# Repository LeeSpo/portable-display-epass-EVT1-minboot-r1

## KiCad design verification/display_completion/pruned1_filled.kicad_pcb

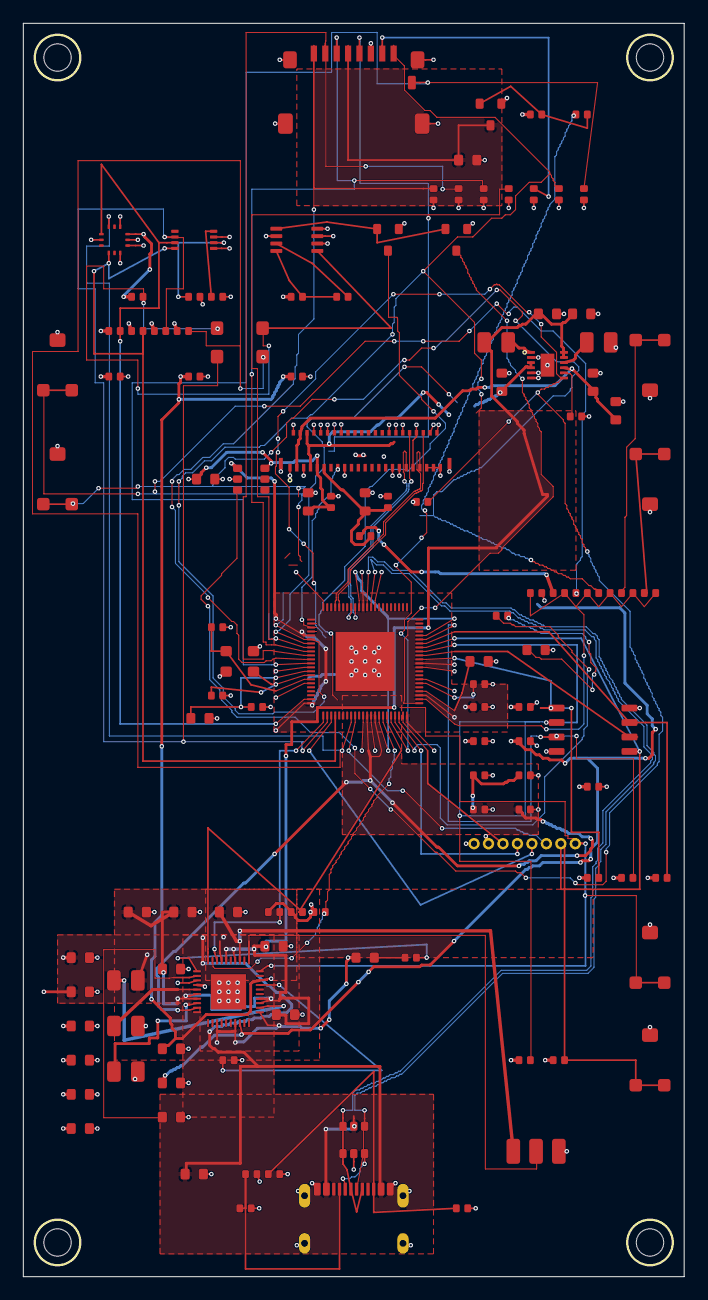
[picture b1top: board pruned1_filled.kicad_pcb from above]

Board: 4 copper layers, 58.0 x 110.0 mm, 124 parts (0 on the bottom side), 83 nets.

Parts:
C1, C2, C4, C5, C6, C7, C8, C9: 22u; 0603
C3, C11, C33, C40, C41, C42, C44: 1u; 0603
C10, C34, C35, C38: 2.2u; 0603
C12, C13: 18p; 0402
C14, C15, C16, C17, C18, C19, C20, C21, C22, C23, C24, C25, C26, C37, C39, C43, C45, C51: 100n; 0402
C29: 4.7u; 0603
C30, C32, C46, C47, C48, C49, C50: 10u; 0603
C31: 10n; 0402
C36: 470n; 0402
D1: CHARGE; LED0603
D2, D3: BAT54; D_SOD123
D5: STATUS; LED0603
D6, D7, D8, D9, D10, D11, D12, D13, D14: PESD4V0; 0402
H1: M2; MountingHole_1
H2: M2; MountingHole_2
H3: M2; MountingHole_3
H4: M2; MountingHole_4
J1: USB4105-GF-A-060; USB4105
J2: 1S LiPo + NTC; BAT3
J3: DEBUG POGO; HDR8
J4: KD024EGOIN152-01; FPC45
J5: MicroSD; MICROSD
L1, L2, L3: 1uH/2A; IND_2x2
L5, L6: 4.7uH; IND_2x2
Q1, Q2: 2N7002; SOT23-3
Q3: AO3401A; SOT23-3
R1, R2: 5.1k; 0402
R3, R15, R16: 4.7k; 0402
R4, R5, R6, R27: 2.2k; 0402
R7, R8, R9, R10, R11, R13, R14, R17, R18, R21, R28: 10k; 0402
R12: 820k; 0402
R20, R22, R26: 100k; 0402
R23, R29, R31: 0R; 0402
R24: 22k; 0402
R25: 47k; 0402
SW1: UP; SW_SIDE
SW2: DOWN; SW_SIDE
SW3: OK; SW_SIDE
SW4: BACK; SW_SIDE
SW5: POWER; SW_SIDE
SW6: FEL; SW_SIDE
U1: AXP2101; QFN40
U2: V851s; QFN88
U3: W25N01GVZEIG; WSON-8
U4: LIS2DW12TR; LGA-12
U5: RV-3028-C7; RTC-8
U6: SN74LVC1G123DCTR; SSOP-8
U8: TPS22918DBVR; SOT23-6
U9: USBLC6-2SC6; SOT23-6
U10: TPS65631DPDR; WSON-12
Y1: 24MHz 10ppm; XTAL4

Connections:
1V8: C10.1, C16.1, C17.1, R22.1, R29.1, U1.18 (ALDO1)
3V3: C4.1, C5.1, C14.1, C15.1, C22.1, D1.1, J3.2 (3V3), L1.2, Q3.2 (S), R3.1, R4.1, R5.1, R7.1, R8.1, R9.1, R10.1, R15.1, R16.1, R17.1, R18.1, R20.1, R28.1, U1.13 (BLDOIN), U1.17 (ALDOIN), U1.21 (FB1), U2.5 (VCC33_PF_PD), U2.22 (VCC_PE), U2.44 (VCC_IO), U2.47 (VDD33), U2.55 (VCC_PC), U2.78 (VCC33_USB), U3.8 (VCC), U8.1 (VIN)
ACCEL_INT_N: D3.1, R18.2, U2.30 (PE6), U4.12 (INT1)
ADC_KEYS: C31.1, R22.2, R23.2, R24.2, R25.2, R26.2, U2.46 (GPADC0)
BAT_NTC: J2.2 (NTC), U1.31 (TS)
CHGLED_A: D1.2, R6.1
CHGLED_N: R6.2, U1.1 (CHGLED)
CORE_0V93: C6.1, C7.1, C18.1, C19.1, C20.1, L2.2, U1.4 (FB3), U2.13 (VDD_SYS0), U2.17 (VDD_SYS1), U2.33 (VDD_SYS2), U2.35 (VDD_SYS3), U2.54 (VDD_SYS4), U2.75 (VDD_SYS5), U2.88 (VDD_SYS6)
DRAM_1V5: C8.1, C9.1, C21.1, L3.2, U1.9 (FB4), U2.34 (VCC_DRAM0), U2.36 (VCC_DRAM1)
DSI_CKN: J4.40 (CLKN), U2.84 (PD5_DSI_CKN)
DSI_CKP: J4.39 (CLKP), U2.85 (PD6_DSI_CKP)
DSI_D0N: J4.36 (D0N), U2.80 (PD1_DSI_D0N)
DSI_D0P: J4.35 (D0P), U2.81 (PD2_DSI_D0P)
E907_RX: J3.6 (E907_RX), U2.31 (PE1)
E907_TX: J3.5 (E907_TX), U2.25 (PE0)
ELVDD: C48.1, J4.6 (ELVDD), J4.7 (ELVDD), U10.3 (OUTP), U10.4 (FBS)
ELVSS: C49.1, C50.1, J4.3 (ELVSS), J4.4 (ELVSS), U10.9 (OUTN)
EL_CT: C51.1, U10.8 (CT)
EL_SWN: L6.1, U10.10 (SWN)
EL_SWP: L5.2, U10.1 (SWP)
GND: C1.2, C2.2, C3.2, C4.2, C5.2, C6.2, C7.2, C8.2, C9.2, C10.2, C11.2, C12.2, C13.2, C14.2, C15.2, C16.2, C17.2, C18.2, C19.2, C20.2, C21.2, C22.2, C24.2, C25.2, C26.2, C29.2, C30.2, C31.2, C32.2, C33.2, C34.2, C35.2, C36.2, C37.2, C38.2, C39.2, C40.2, C41.2, C42.2, C43.2, C44.2, C45.2, C46.2, C47.2, C48.2, C49.2, C50.2, C51.2, D5.2, D6.2, D7.2, D8.2, D9.2, D10.2, D11.2, D12.2, D13.2, D14.2, J1.A1 (GND), J1.A12 (GND), J1.B1 (GND), J1.B12 (GND), J1.SH1 (SHIELD), J1.SH2 (SHIELD), J1.SH3 (SHIELD), J1.SH4 (SHIELD), J2.3 (GND), J3.1 (GND), J4.1 (GND), J4.2 (GND), J4.5 (GND), J4.8 (GND), J4.10 (GND), J4.12 (GND), J4.17 (GND), J4.30 (GND), J4.31 (IM1), J4.32 (IM0), J4.33 (GND), J4.34 (GND), J4.37 (GND), J4.38 (GND), J4.41 (GND), J4.42 (GND), J4.43 (MTP), J4.44 (GND), J4.45 (GND), J4.MP1 (MOUNT), J4.MP2 (MOUNT), J5.6 (VSS), J5.10 (SH), J5.11 (SH), J5.12 (SH), J5.13 (SH), L6.2, Q1.2 (S), Q2.2 (S), R1.2, R2.2, R13.2, R14.2, SW1.3 (GND), SW2.3 (GND), SW3.3 (GND), SW4.3 (GND), SW5.3 (GND), SW6.3 (GND), U1.3 (GND), U1.41 (EPAD), U2.51 (AGND), U2.89 (EPAD), U3.4 (GND), U4.6 (GND), U4.7 (RES), U4.8 (GND), U5.5 (VSS), U6.2 (GND), U8.2 (GND), U9.2 (GND), U10.2 (PGND), U10.5 (AGND), U10.6 (GND), U10.13 (EPAD), Y1.2 (GND), Y1.4 (GND)
I2C0_SCL: R15.2, U2.21 (PE4), U4.1 (SCL), U5.3 (SCL)
I2C0_SDA: R16.2, U2.26 (PE5), U4.4 (SDA), U5.4 (SDA)
KEY_BACK: R26.1, SW4.1 (KEY), SW4.2 (KEY)
KEY_DOWN: R24.1, SW2.1 (KEY), SW2.2 (KEY)
KEY_OK: R25.1, SW3.1 (KEY), SW3.2 (KEY)
KEY_UP: R23.1, SW1.1 (KEY), SW1.2 (KEY)
LCD_1V8: C44.1, C45.1, J4.11 (VDDIO), R29.2
LCD_3V3: C29.1, C42.1, C43.1, J4.9 (VCI), U8.6 (VOUT)
LCD_EN: R31.2, U2.4 (PD21), U8.3 (ON), U10.7 (CTRL)
LCD_RST: J4.16 (RESX), U2.2 (PD19)
LCD_SWIRE: J4.14 (SWIRE), R31.1
LCD_TE: J4.15 (TE), U2.3 (PD20)
LX_3V3: L1.1, U1.22 (LX1)
LX_CORE: L2.1, U1.5 (LX3)
LX_DRAM: L3.1, U1.8 (LX4)
NAND_CLK: U2.57 (PC0_SPI0_CLK), U3.6 (CLK)
NAND_CS: R7.2, U2.56 (PC1_SPI0_CS), U3.1 (CS)
NAND_HOLD: R9.2, U2.60 (PC5_SPI0_HOLD), U3.7 (HOLD)
NAND_MISO: R28.2, U2.58 (PC3_SPI0_MISO_BOOT1), U3.2 (MISO)
NAND_MOSI: J3.7 (FEL_PC2), R10.2, SW6.1 (FEL_PC2), SW6.2 (FEL_PC2), U2.59 (PC2_SPI0_MOSI_BOOT0), U3.5 (MOSI)
NAND_WP: R8.2, U2.61 (PC4_SPI0_WP), U3.3 (WP)
PMIC_BACKUP: C39.1, U1.27 (VBACKUP)
PMIC_IRQ_N: R3.2, U1.38 (IRQ), U2.23 (PE2)
PMIC_SCL: R4.2, U1.40 (SCK), U2.39 (PH13)
PMIC_SDA: R5.2, U1.39 (SDA), U2.38 (PH14)
PWRON_N: J3.8 (PWRON_N), Q1.3 (D), SW5.1 (PWRON), SW5.2 (PWRON), U1.30 (PWRON)
RTC_3V3: C24.1, C25.1, C26.1, C33.1, R11.1, R12.1, U1.28 (VRTC), U4.2 (CS), U4.9 (VDD), U4.10 (VDDIO), U5.7 (VDD), U6.6 (B), U6.7 (CLR), U6.8 (VCC)
RTC_EVI: R14.1, U5.8 (EVI)
RTC_INT_N: D2.1, R17.2, U2.24 (PE7), U5.2 (INT)
RTC_VBACKUP: R13.1, U5.6 (VBACKUP)
SD_3V3: C30.1, J5.4 (VDD), Q3.3 (D)
SD_CLK: D9.1, J5.5 (CLK), U2.8 (PF2_SDC0_CLK)
SD_CMD: D8.1, J5.3 (CMD), U2.9 (PF3_SDC0_CMD)
SD_D0: D10.1, J5.7 (DAT0), U2.7 (PF1_SDC0_D0)
SD_D1: D11.1, J5.8 (DAT1), U2.6 (PF0_SDC0_D1)
SD_D2: D6.1, J5.1 (DAT2), U2.11 (PF5_SDC0_D2)
SD_D3: D7.1, J5.2 (DAT3), U2.10 (PF4_SDC0_D3)
SD_DET: D12.1, J5.9 (CD), U2.12 (PF6_DBG_CLK)
SD_PWR_EN: R21.1, U2.40 (PH12)
SD_PWR_GATE: Q3.1 (G), R20.2, R21.2
SOC_AVCC: C35.1, U2.48 (AVCC)
SOC_LDO_1V8: C34.1, C37.1, U2.14 (VCC_LDOA_PLL), U2.37 (VDD18_DRAM), U2.62 (VCC_PA_MCSI), U2.79 (VCC18_MDSI)
STATUS_LED: R27.1, U2.41 (PH11)
STATUS_LED_A: D5.1, R27.2
UART0_RX: J3.4 (UART0_RX), U2.42 (PH10)
UART0_TX: J3.3 (UART0_TX), U2.43 (PH9)
USB_CC1: D13.1, J1.A5 (CC1), R1.1
USB_CC2: D14.1, J1.B5 (CC2), R2.1
USB_DM: J1.A7 (DM1), J1.B7 (DM2), U2.77 (USB0_DM), U9.3 (I/O2), U9.4 (I/O2)
USB_DP: J1.A6 (DP1), J1.B6 (DP2), U2.76 (USB0_DP), U9.1 (I/O1), U9.6 (I/O1)
VBAT: C3.1, J2.1 (VBAT), U1.33 (BAT)
VBUS: C32.1, J1.A4 (VBUS), J1.A9 (VBUS), J1.B4 (VBUS), J1.B9 (VBUS), U1.37 (VBUS), U9.5 (VBUS)
VRA1: C36.1, U2.50 (VRA1)
VREF: C11.1, U1.2 (VREF)
VSYS: C1.1, C2.1, C38.1, C40.1, C41.1, C46.1, C47.1, L5.1, U1.6 (VIN3), U1.7 (VIN4), U1.23 (VIN1), U1.24 (VIN2), U1.34 (VSYS), U1.36 (VMID), U10.11 (AVIN), U10.12 (PVIN)
WAKE_CEXT: C23.2, U6.3 (CEXT)
WAKE_PULSE: Q1.1 (G), Q2.1 (G), U6.1 (Q)
WAKE_PULSE_N: Q2.3 (D), U2.45 (PH0)
WAKE_REQ_N: D2.2, D3.2, R11.2, U6.5 (A)
WAKE_REXT: C23.1, R12.2, U6.4 (REXT_CEXT)
XIN: C12.1, U2.16 (DXIN), Y1.1 (XIN)
XOUT: C13.1, U2.15 (DXOUT), Y1.3 (XOUT)

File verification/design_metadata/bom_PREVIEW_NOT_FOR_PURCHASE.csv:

Reference,Value,Footprint,Manufacturer Part,LCSC,Datasheet,DNP,Status
J1,USB4105-GF-A-060,Sameat:USB4105,USB4105-GF-A-060,C3025063,https://gct.co/files/drawings/usb4105.pdf,no,ENGINEERING PREVIEW
R1,5.1k,Sameat:0402,0402 5.1k 1%,C25905,,no,ENGINEERING PREVIEW
R2,5.1k,Sameat:0402,0402 5.1k 1%,C25905,,no,ENGINEERING PREVIEW
U1,AXP2101,Sameat:QFN40,AXP2101,C3036461,https://www.x-powers.com/en.php/Info/product_detail/article_id/95,no,ENGINEERING PREVIEW
L1,1uH/2A,Sameat:IND_2x2,1uH 2A shielded,,,no,ENGINEERING PREVIEW
L2,1uH/2A,Sameat:IND_2x2,1uH 2A shielded,,,no,ENGINEERING PREVIEW
L3,1uH/2A,Sameat:IND_2x2,1uH 2A shielded,,,no,ENGINEERING PREVIEW
C1,22u,Sameat:0603,0603 22u X5R,,,no,ENGINEERING PREVIEW
C2,22u,Sameat:0603,0603 22u X5R,,,no,ENGINEERING PREVIEW
C3,1u,Sameat:0603,0603 1u X5R,,,no,ENGINEERING PREVIEW
C4,22u,Sameat:0603,0603 22u X5R,,,no,ENGINEERING PREVIEW
C5,22u,Sameat:0603,0603 22u X5R,,,no,ENGINEERING PREVIEW
C6,22u,Sameat:0603,0603 22u X5R,,,no,ENGINEERING PREVIEW
C7,22u,Sameat:0603,0603 22u X5R,,,no,ENGINEERING PREVIEW
C8,22u,Sameat:0603,0603 22u X5R,,,no,ENGINEERING PREVIEW
C9,22u,Sameat:0603,0603 22u X5R,,,no,ENGINEERING PREVIEW
C10,2.2u,Sameat:0603,0603 2.2u X5R,,,no,ENGINEERING PREVIEW
C11,1u,Sameat:0603,0603 1u X5R,,,no,ENGINEERING PREVIEW
J2,1S LiPo + NTC,Sameat:BAT3,S3B-PH-SM4-TB(LF)(SN),C265101,,no,ENGINEERING PREVIEW
SW5,POWER,Sameat:SW_SIDE,GT-TC072B-H045-L1,C5117859,,no,ENGINEERING PREVIEW
R3,4.7k,Sameat:0402,,C25900,,no,ENGINEERING PREVIEW
R4,2.2k,Sameat:0402,,C25879,,no,ENGINEERING PREVIEW
R5,2.2k,Sameat:0402,,C25879,,no,ENGINEERING PREVIEW
D1,CHARGE,Sameat:LED0603,0603 Green LED,,,no,ENGINEERING PREVIEW
R6,2.2k,Sameat:0402,,C25879,,no,ENGINEERING PREVIEW
U9,USBLC6-2SC6,Sameat:SOT23-6,USBLC6-2SC6,C2827654,https://www.st.com/resource/en/datasheet/usblc6-2.pdf,no,ENGINEERING PREVIEW
D13,PESD4V0,Sameat:0402,PESD4V0Y1BBSF,,,no,ENGINEERING PREVIEW
D14,PESD4V0,Sameat:0402,PESD4V0Y1BBSF,,,no,ENGINEERING PREVIEW
C32,10u,Sameat:0603,0603 10u X5R,,,no,ENGINEERING PREVIEW
C33,1u,Sameat:0603,0603 1u X5R,,,no,ENGINEERING PREVIEW
C38,2.2u,Sameat:0603,,,,no,ENGINEERING PREVIEW
C39,100n,Sameat:0402,,,,no,ENGINEERING PREVIEW
C40,1u,Sameat:0603,,,,no,ENGINEERING PREVIEW
C41,1u,Sameat:0603,,,,no,ENGINEERING PREVIEW
U2,V851s,Sameat:QFN88,V851s,C5365286,https://www.allwinnertech.com/index.php?a=index&c=product&id=118,no,ENGINEERING PREVIEW
Y1,24MHz 10ppm,Sameat:XTAL4,24MHz 10ppm 3225,,,no,ENGINEERING PREVIEW
C12,18p,Sameat:0402,,,,no,ENGINEERING PREVIEW
C13,18p,Sameat:0402,,,,no,ENGINEERING PREVIEW
C34,2.2u,Sameat:0603,,,,no,ENGINEERING PREVIEW
C35,2.2u,Sameat:0603,,,,no,ENGINEERING PREVIEW
C36,470n,Sameat:0402,,,,no,ENGINEERING PREVIEW
C37,100n,Sameat:0402,,,,no,ENGINEERING PREVIEW
C14,100n,Sameat:0402,0402 100n X7R,C1525,,no,ENGINEERING PREVIEW
C15,100n,Sameat:0402,0402 100n X7R,C1525,,no,ENGINEERING PREVIEW
C16,100n,Sameat:0402,0402 100n X7R,C1525,,no,ENGINEERING PREVIEW
C17,100n,Sameat:0402,0402 100n X7R,C1525,,no,ENGINEERING PREVIEW
C18,100n,Sameat:0402,0402 100n X7R,C1525,,no,ENGINEERING PREVIEW
C19,100n,Sameat:0402,0402 100n X7R,C1525,,no,ENGINEERING PREVIEW
C20,100n,Sameat:0402,0402 100n X7R,C1525,,no,ENGINEERING PREVIEW
C21,100n,Sameat:0402,0402 100n X7R,C1525,,no,ENGINEERING PREVIEW
U3,W25N01GVZEIG,Sameat:WSON-8,W25N01GVZEIG,C907680,https://www.winbond.com/hq/product/code-storage-flash-memory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,no,ENGINEERING PREVIEW
C22,100n,Sameat:0402,,C1525,,no,ENGINEERING PREVIEW
R7,10k,Sameat:0402,,,,no,ENGINEERING PREVIEW
R8,10k,Sameat:0402,,,,no,ENGINEERING PREVIEW
R9,10k,Sameat:0402,,,,no,ENGINEERING PREVIEW
J3,DEBUG POGO,Sameat:HDR8,,,,no,ENGINEERING PREVIEW
SW6,FEL,Sameat:SW_SIDE,GT-TC072B-H045-L1,C5117859,,no,ENGINEERING PREVIEW
R10,10k,Sameat:0402,,,,no,ENGINEERING PREVIEW
R28,10k,Sameat:0402,,,,no,ENGINEERING PREVIEW
U4,LIS2DW12TR,Sameat:LGA-12,LIS2DW12TR,C189624,https://www.st.com/resource/en/datasheet/lis2dw12.pdf,no,ENGINEERING PREVIEW
U5,RV-3028-C7,Sameat:RTC-8,RV-3028-C7-32.768kHz-1ppm-TA-QC,C3019759,https://www.microcrystal.com/fileadmin/Media/Products/RTC/Ap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,no,ENGINEERING PREVIEW
U6,SN74LVC1G123DCTR,Sameat:SSOP-8,SN74LVC1G123DCTR,,https://www.ti.com/lit/ds/symlink/sn74lvc1g123.pdf,no,ENGINEERING PREVIEW
Q1,2N7002,Sameat:SOT23-3,2N7002,C8545,,no,ENGINEERING PREVIEW
Q2,2N7002,Sameat:SOT23-3,2N7002,C8545,,no,ENGINEERING PREVIEW
R11,10k,Sameat:0402,,,,no,ENGINEERING PREVIEW
R12,820k,Sameat:0402,,,,no,ENGINEERING PREVIEW
C23,100n,Sameat:0402,,,,no,ENGINEERING PREVIEW
R13,10k,Sameat:0402,,,,no,ENGINEERING PREVIEW
R14,10k,Sameat:0402,,,,no,ENGINEERING PREVIEW
R15,4.7k,Sameat:0402,,,,no,ENGINEERING PREVIEW
R16,4.7k,Sameat:0402,,,,no,ENGINEERING PREVIEW
R17,10k,Sameat:0402,,,,no,ENGINEERING PREVIEW
R18,10k,Sameat:0402,,,,no,ENGINEERING PREVIEW
D2,BAT54,Sameat:D_SOD123,,,,no,ENGINEERING PREVIEW
D3,BAT54,Sameat:D_SOD123,,,,no,ENGINEERING PREVIEW
C24,100n,Sameat:0402,,C1525,,no,ENGINEERING PREVIEW
C25,100n,Sameat:0402,,C1525,,no,ENGINEERING PREVIEW
C26,100n,Sameat:0402,,C1525,,no,ENGINEERING PREVIEW
J4,TFT-H035B22WVIST8N20_V3-0,Sameat:FPC20,FH12-20S-0.5SH(55),C596730,https://www.hotlcd.com/productdetail/1973,no,ENGINEERING PREVIEW
U7,TPS61169DCKR,Sameat:SC70-5,TPS61169DCKR,C71045,https://www.ti.com/lit/ds/symlink/tps61169.pdf,no,ENGINEERING PREVIEW
L4,10uH/1.5A,Sameat:IND_2x2,,,,no,ENGINEERING PREVIEW
D4,SS16,Sameat:D_SOD123,,,,no,ENGINEERING PREVIEW
R19,2.55R 1%,Sameat:0603,,,,no,ENGINEERING PREVIEW
C27,1u/25V,Sameat:0603,,,,no,ENGINEERING PREVIEW
C28,100n,Sameat:0402,,,,no,ENGINEERING PREVIEW
U8,TPS22918DBVR,Sameat:SOT23-6,TPS22918DBVR,,https://www.ti.com/lit/ds/symlink/tps22918.pdf,no,ENGINEERING PREVIEW
C29,4.7u,Sameat:0603,,,,no,ENGINEERING PREVIEW
J5,MicroSD,Sameat:MICROSD,MUP-M617-2,C5205359,,no,ENGINEERING PREVIEW
Q3,AO3401A,Sameat:SOT23-3,AO3401A,C15127,,no,ENGINEERING PREVIEW
R20,100k,Sameat:0402,,,,no,ENGINEERING PREVIEW
R21,10k,Sameat:0402,,,,no,ENGINEERING PREVIEW
C30,10u,Sameat:0603,,,,no,ENGINEERING PREVIEW
D6,PESD4V0,Sameat:0402,PESD4V0Y1BBSF,,,no,ENGINEERING PREVIEW
D7,PESD4V0,Sameat:0402,PESD4V0Y1BBSF,,,no,ENGINEERING PREVIEW
D8,PESD4V0,Sameat:0402,PESD4V0Y1BBSF,,,no,ENGINEERING PREVIEW
D9,PESD4V0,Sameat:0402,PESD4V0Y1BBSF,,,no,ENGINEERING PREVIEW
D10,PESD4V0,Sameat:0402,PESD4V0Y1BBSF,,,no,ENGINEERING PREVIEW
D11,PESD4V0,Sameat:0402,PESD4V0Y1BBSF,,,no,ENGINEERING PREVIEW
D12,PESD4V0,Sameat:0402,PESD4V0Y1BBSF,,,no,ENGINEERING PREVIEW
SW1,UP,Sameat:SW_SIDE,GT-TC072B-H045-L1,C5117859,,no,ENGINEERING PREVIEW
SW2,DOWN,Sameat:SW_SIDE,GT-TC072B-H045-L1,C5117859,,no,ENGINEERING PREVIEW
SW3,OK,Sameat:SW_SIDE,GT-TC072B-H045-L1,C5117859,,no,ENGINEERING PREVIEW
SW4,BACK,Sameat:SW_SIDE,GT-TC072B-H045-L1,C5117859,,no,ENGINEERING PREVIEW
R22,100k,Sameat:0402,,,,no,ENGINEERING PREVIEW
R23,0R,Sameat:0402,,,,no,ENGINEERING PREVIEW
R24,22k,Sameat:0402,,,,no,ENGINEERING PREVIEW
R25,47k,Sameat:0402,,,,no,ENGINEERING PREVIEW
R26,100k,Sameat:0402,,,,no,ENGINEERING PREVIEW
C31,10n,Sameat:0402,,,,no,ENGINEERING PREVIEW
D5,STATUS,Sameat:LED0603,0603 Blue LED,,,no,ENGINEERING PREVIEW
R27,2.2k,Sameat:0402,,,,no,ENGINEERING PREVIEW
